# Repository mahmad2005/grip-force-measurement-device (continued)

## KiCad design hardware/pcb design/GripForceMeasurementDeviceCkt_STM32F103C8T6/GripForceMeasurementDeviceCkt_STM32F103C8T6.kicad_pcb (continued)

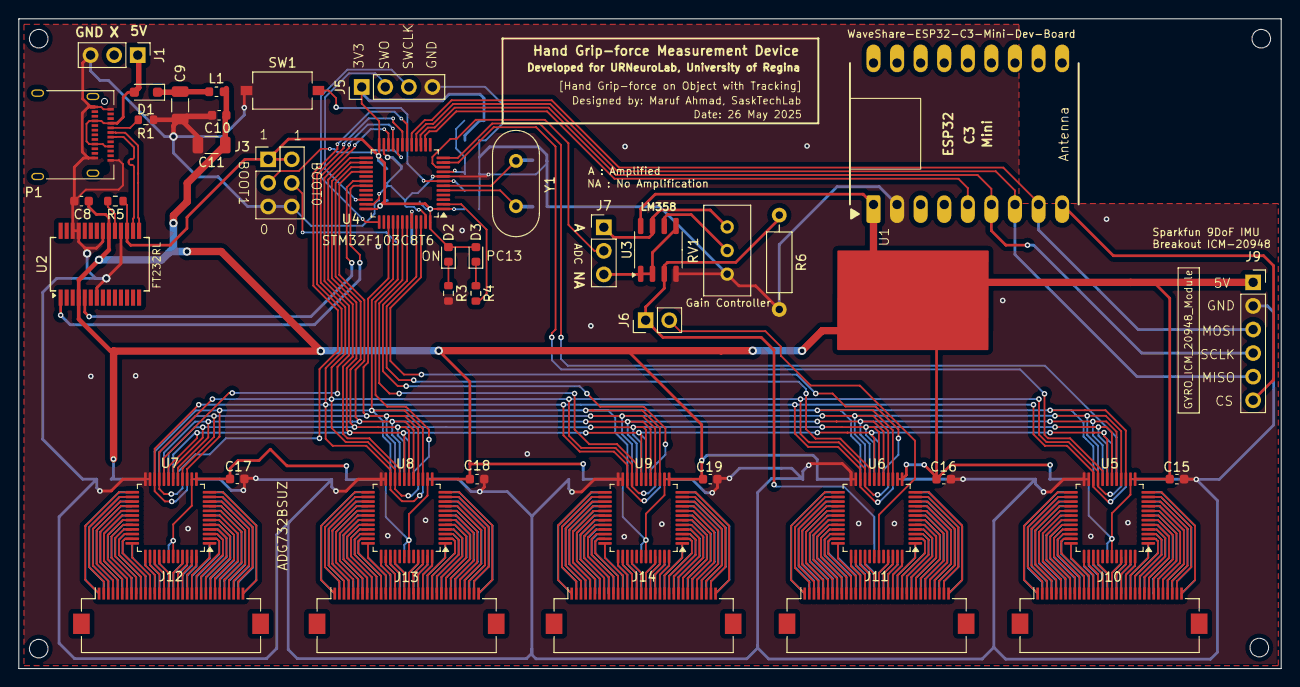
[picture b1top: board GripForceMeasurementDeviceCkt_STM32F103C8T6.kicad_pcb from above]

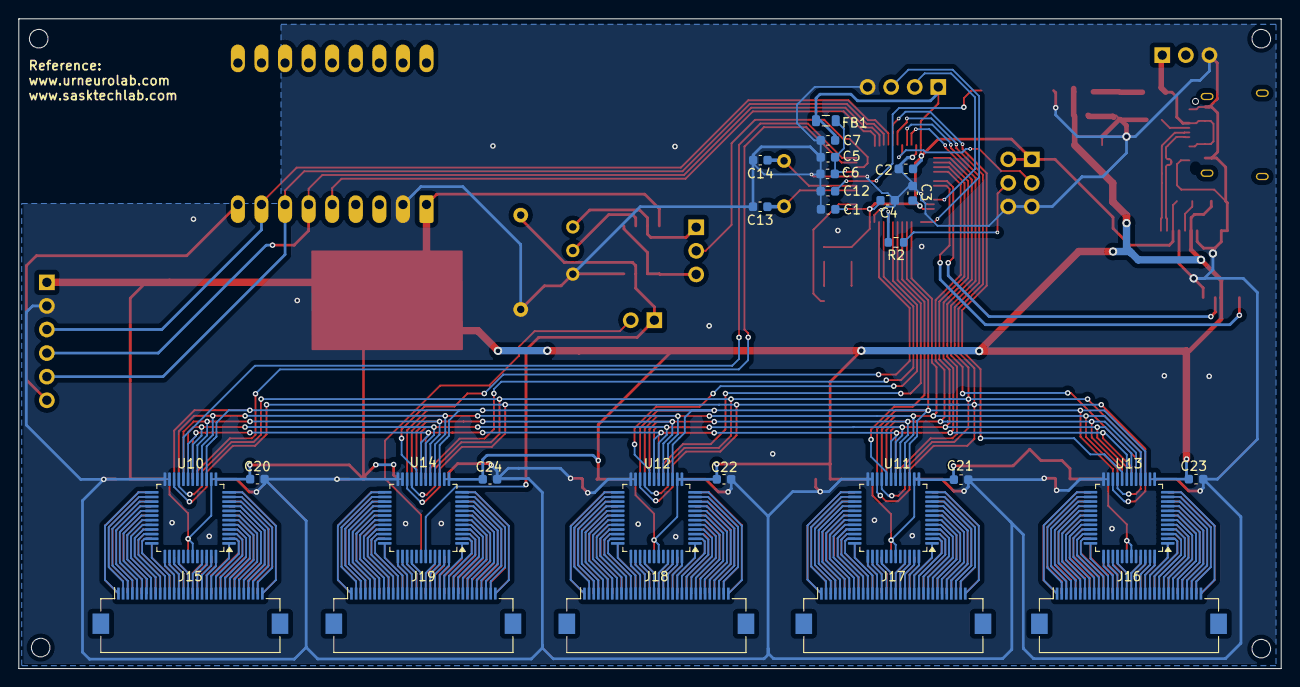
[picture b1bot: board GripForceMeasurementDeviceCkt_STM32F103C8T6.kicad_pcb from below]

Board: 2 copper layers, 136.0 x 70.0 mm, 69 parts (27 on the bottom side), 371 nets.

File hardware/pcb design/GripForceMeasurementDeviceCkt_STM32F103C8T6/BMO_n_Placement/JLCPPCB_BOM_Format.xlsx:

Comment | Designator | Footprint | JLCPCB Part # (optional)
L | L1 | L_0805_2012Metric
100n | C10,C17,C19,C16,C1,C15,C18,C2,C3,C22,C12,C20,C4,C24,C21,C5,C23 | C_0603_1608Metric
ADG732BSUZ | U5,U8,U6,U7,U9,U10,U11,U12,U14,U13 | TQFP-48_7x7mm_P0.5mm
5.1k | R1 | R_0603_1608Metric
Conn_01x02 | J18 | PinHeader_1x02_P2.54mm_Vertical
STM32F103C8Tx | U4 | LQFP-48_7x7mm_P0.5mm
8MHz | Y1 | Crystal_HC49-4H_Vertical
330R | R4 | R_Axial_DIN0207_L6.3mm_D2.5mm_P7.62mm_Horizontal
USB_C_Plug_USB2.0 | P1 | USB_C_Receptacle_Amphenol_12401610E4-2A
Gyro_Sensor_ICM_20948_SparkFun_Module | J7 | PinSocket_1x06_P2.54mm_Vertical
500k | RV1 | Potentiometer_Bourns_3296W_Vertical
Conn_01x32 | J9,J10,J12,J8,J11,J13,J14,J16,J17,J15 | Hirose_FH12-32S-0.5SH_1x32-1MP_P0.50mm_Horizontal
Power_Conn | J19 | PinHeader_1x03_P2.54mm_Vertical
1N5819 | D1 | D_MicroMELF
Boot Conn | J2 | PinHeader_2x03_P2.54mm_Vertical
4.7u | C11 | C_1206_3216Metric
SW_Push | SW1 | SW_Tactile_SPST_NO_Straight_CK_PTS636Sx25SMTRLFS
10k | R3,R2 | R_0603_1608Metric
ESP32-C3-Mini | U1 | ESP32-C3-Mini-through-hole
10u | C9 | C_1206_3216Metric
LM358 | U3 | SO-8_3.9x4.9mm_P1.27mm
Conn_01x03 | J6 | PinHeader_1x03_P2.54mm_Vertical
FT232RL | U2 | SSOP-28_5.3x10.2mm_P0.65mm
SWD | J5 | PinHeader_1x04_P2.54mm_Vertical
22p | C14,C13 | C_0402_1005Metric
10n | C6 | C_0603_1608Metric
1u | C7,C8 | C_0603_1608Metric
FerriteBead | FB1 | L_0805_2012Metric

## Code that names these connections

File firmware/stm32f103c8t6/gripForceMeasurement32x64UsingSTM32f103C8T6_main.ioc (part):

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Mcu.Name=STM32F103C(8-B)Tx
Mcu.Package=LQFP48
Mcu.UserName=STM32F103C8Tx
PA0-WKUP.Signal=ADCx_IN0
PA10.Mode=Asynchronous
PA10.Signal=USART1_RX
PA13.Mode=Serial_Wire
PA13.Signal=SYS_JTMS-SWDIO
PA14.Mode=Serial_Wire
PA14.Signal=SYS_JTCK-SWCLK
PA4.Mode=NSS_Signal_Hard_Input
PA4.Signal=SPI1_NSS
PA5.Mode=Full_Duplex_Slave
PA5.Signal=SPI1_SCK
PA6.Mode=Full_Duplex_Slave
PA6.Signal=SPI1_MISO
PA7.Mode=Full_Duplex_Slave
PA7.Signal=SPI1_MOSI
PA9.Mode=Asynchronous
PA9.Signal=USART1_TX
PC13-TAMPER-RTC.Signal=GPIO_Output
PD0-OSC_IN.Mode=HSE-External-Oscillator
PD0-OSC_IN.Signal=RCC_OSC_IN
PD1-OSC_OUT.Mode=HSE-External-Oscillator
PD1-OSC_OUT.Signal=RCC_OSC_OUT
RCC.SYSCLKFreq_VALUE=72000000
RCC.SYSCLKSource=RCC_SYSCLKSOURCE_PLLCLK
board=custom

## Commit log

2025-03-17 Project has been created. Currently working on schematic design of the HGF device's PCB
2025-03-20 initial design of schemetic has completed
2025-05-14 complete schemetic design. working on PCB
2025-05-19 updated PCB design
2025-05-19 readme.md
2025-05-19 udpated readme
2025-05-20 some photos added
2025-05-20 fix the rotation of an image
2025-05-21 pcb trace complete
2025-05-22 re-configured the pins connection again
2025-05-24 bluetooth module has removed
2025-05-26 GND ground layer filled
2025-06-25 Firmware develepment initiated
2025-08-17 New Design sensor pad visualization through UART completed
2025-08-18 mcu to pc through SPI, UDP pressure data visualization system prototype implemented
2025-08-30 update firmware and visualization software
2025-08-30 updated documentation
2025-09-03 pressueValueWith-gyro-accel-magnato-val with viz added
2025-09-03 updated readme and folder name
2025-09-04 added 3d object in visualization
2025-09-04 updated 3d cube to cylindrical object in visualization
2025-09-24 note update
2026-01-13 added video
2026-05-29 updated final 3d vizualisation program
2026-06-01 updated 3d viewr
2026-06-05 update 4k video output
2026-06-19 pose precision earned and new viewer implemented
2026-06-19 git ignore added
2026-06-19 4k video process folder moved
2026-06-23 new Grip Force 3D Simulator Software implemented with lots of improvements on object tracking precision. Pressure distribution heatmap added. Recorder Added
2026-06-23 docs: Add comprehensive AprilTag processing guide with script variants and frame range examples
    - Document all three AprilTag detector script variants and their use cases
    - Explain key parameters (--start-frame, --end-frame, --process-fps, etc.)
    - Add three practical usage examples: quick test, full video export, and frame range processing
    - Document output files created by each command (annotated video, viewer HTML/JSON)
    - Add processing tips for optimization (speed vs. accuracy trade-offs)
    - Clarify use of detect_apriltag_pose_fixed11_4k_option3_single_state_start_end_frame.py for partial video processing
2026-06-24 Improve viewer synchronization, graph zoom, and persistent standalone layout
    * Fixed timeline sync between 3D viewer, annotated video, pressure distribution, and IMU data
    * Kept viewer_data.json as the main 3D/video timeline
    * Added pressure/IMU start-frame sync without changing native playback speed
    * Added oscilloscope-style time and magnitude zoom controls for pressure and IMU graphs
    * Improved annotated video following behavior
    * Added persistent floating panel layout for position, size, and minimized state
2026-06-24 new screenshot added
2026-06-24 viewer file name changed
2026-06-24 demo video updated in readme.md
2026-06-24 video with voiceover updated
